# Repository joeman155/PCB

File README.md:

This is a repository of PCB (Printed Circuit Boards) that I have created.

internal_board - Internal board to the High Altitude Balloon that I am creating
                      - pcb1 - Arduino Shield with pressure sensor, serial voltage level converter, 
                               transistor for relay actuator circuit, circuitry for measuring psu voltage
                      - pcb3 - Copernicus GPS, Relay, PSU, switches, RFD900 power/data connectors.
                      - pcb4 - 5 volt 3amp Switch Mode PSU

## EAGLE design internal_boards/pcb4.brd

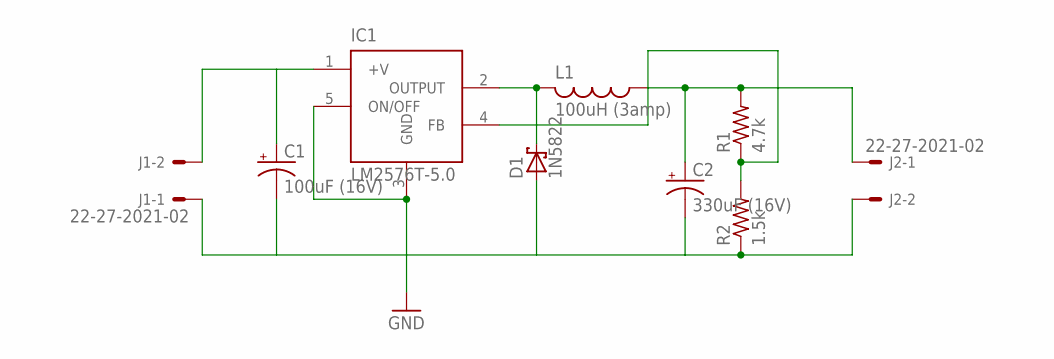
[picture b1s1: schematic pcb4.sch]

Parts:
C1: 100uF (16V); TT2D6
C2: 330uF (16V); TT5D10
D1: 1N5822; C4111-15
IC1: LM2576T-5.0; TO220-5
J1, J2: 22-27-2021-02; 6410-02
L1: 100uH (3amp); TJ3-U1
R1: 4.7k; 0204/7
R2: 1.5k; 0204/7

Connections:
GND: C1.-, C2.-, D1.A, IC1.3 (GND), IC1.5 (ON/OFF), J1.1, J2.2, R2.1
unnamed: IC1.4 (FB), R1.1, R2.2
unnamed: C1.+, IC1.1 (+V), J1.2
unnamed: D1.C, IC1.2 (OUTPUT), L1.2
unnamed: C2.+, J2.1, L1.1, R1.2

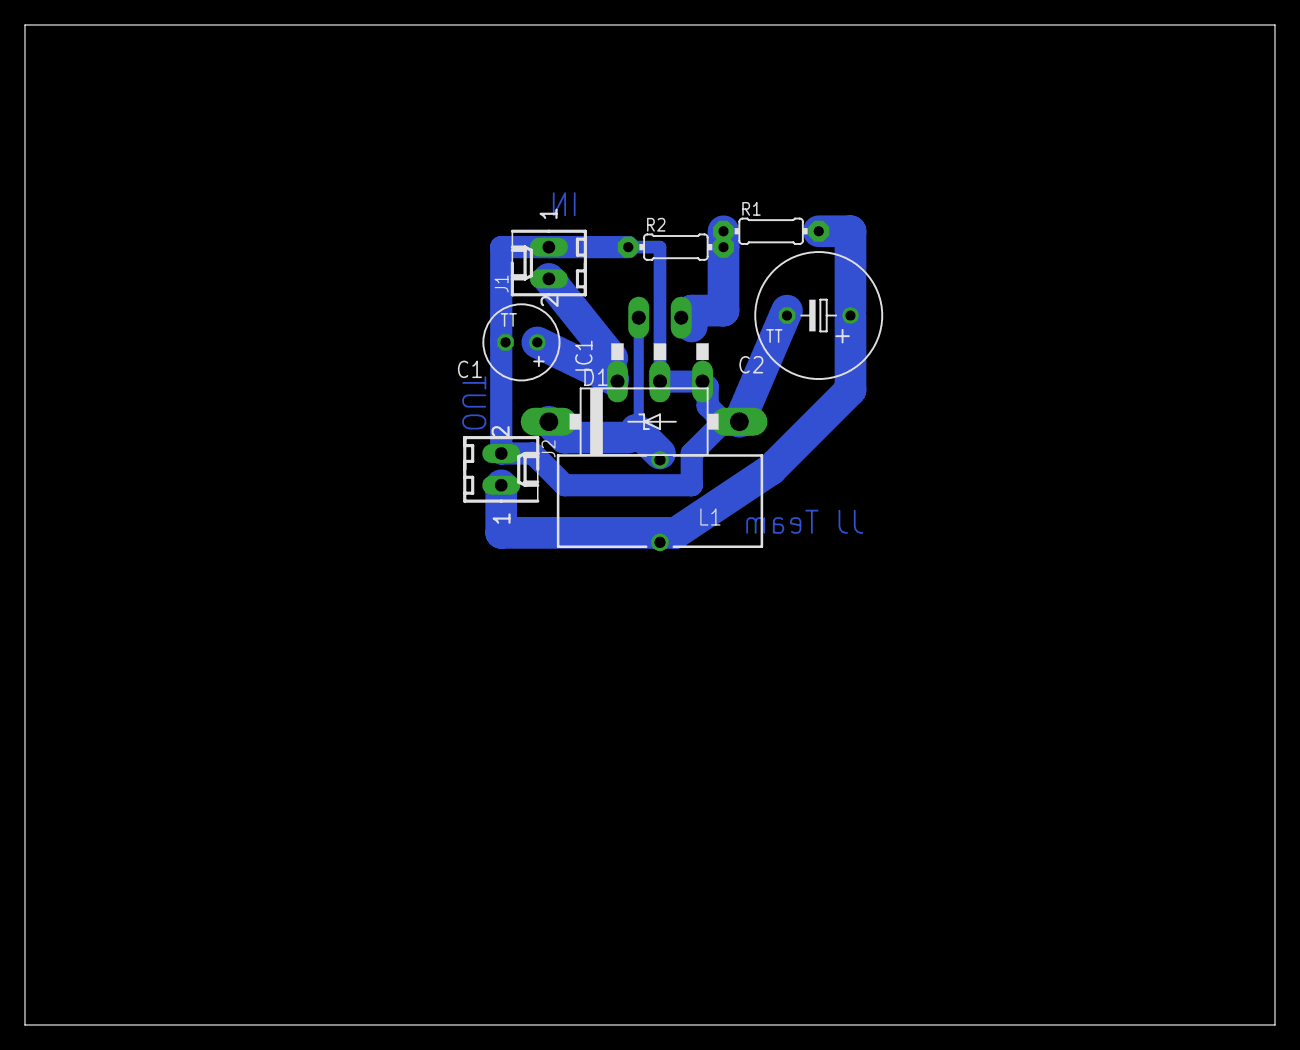
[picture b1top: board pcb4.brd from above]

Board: 2 copper layers, 100.0 x 80.0 mm, 9 parts (0 on the bottom side), 5 nets.

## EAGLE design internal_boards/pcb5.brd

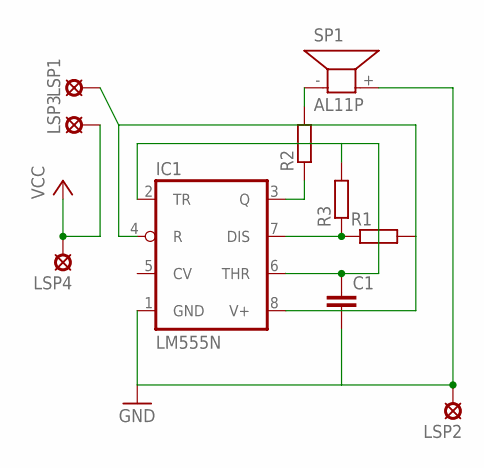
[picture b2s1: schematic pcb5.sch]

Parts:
C1: C-EU025-024X044; C025-024X044
IC1: LM555N; DIL08
LSP1, LSP2, LSP3, LSP4: MCS08
R1, R2: R-EU_0204_7; 0204/7
R3: R-EU_0204/7; 0204/7
SP1: AL11P

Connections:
GND: C1.2, IC1.1 (GND), LSP2.MP, SP1.+ (2)
unnamed: IC1.3 (Q), R2.1
unnamed: IC1.7 (DIS), R1.1, R3.1
unnamed: R2.2, SP1.- (1)
unnamed: C1.1, IC1.2 (TR), IC1.6 (THR), R3.2
unnamed: IC1.4 (R), IC1.8 (V+), LSP1.MP, R1.2
VCC: LSP3.MP, LSP4.MP

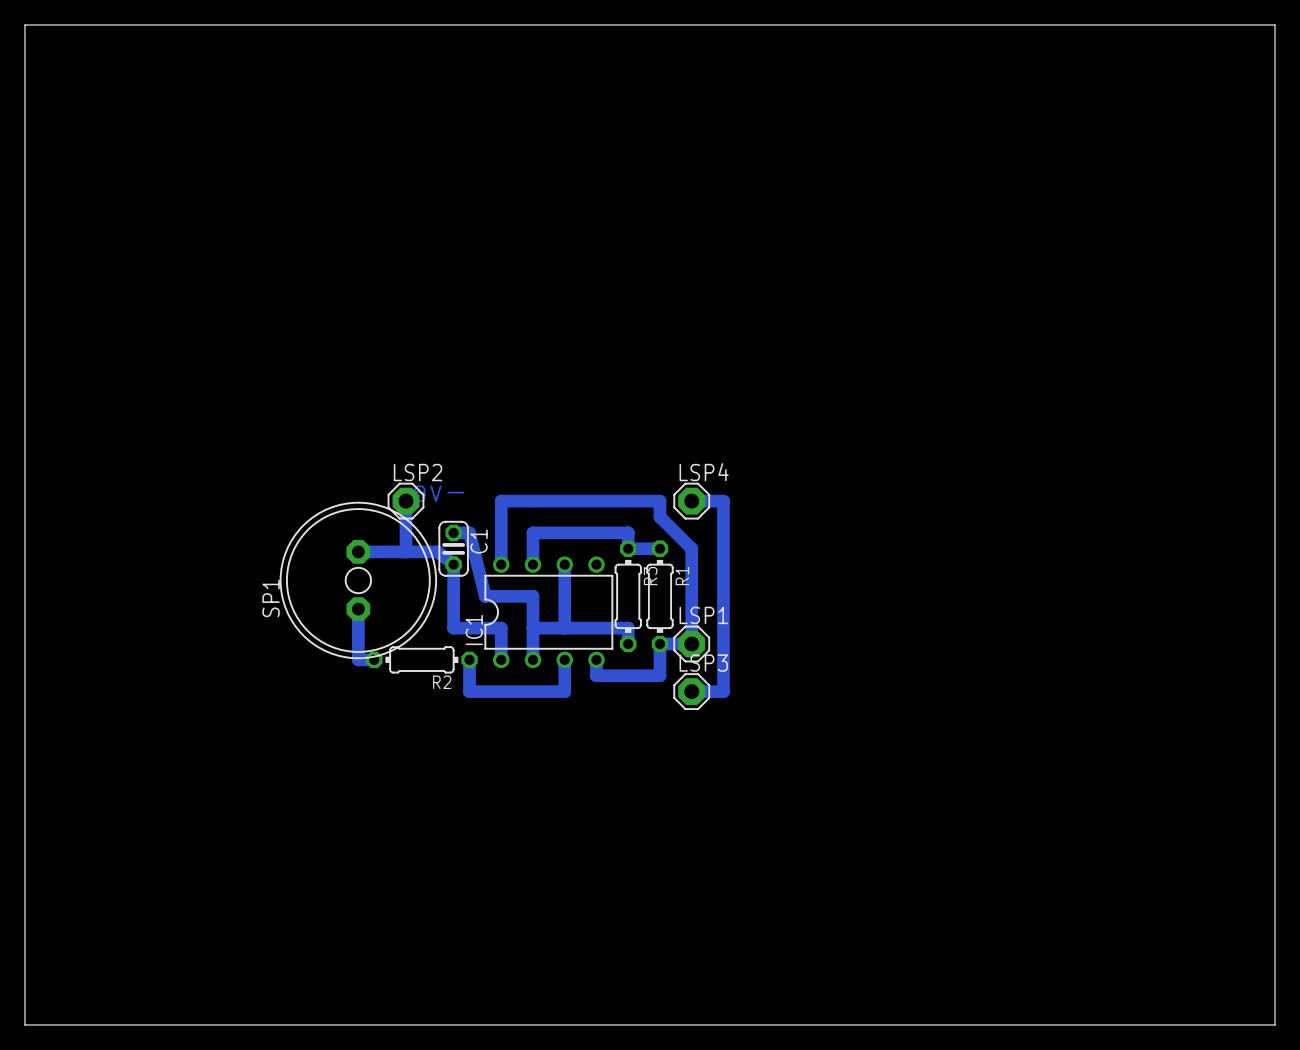
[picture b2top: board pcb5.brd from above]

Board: 2 copper layers, 100.0 x 80.0 mm, 10 parts (0 on the bottom side), 7 nets.

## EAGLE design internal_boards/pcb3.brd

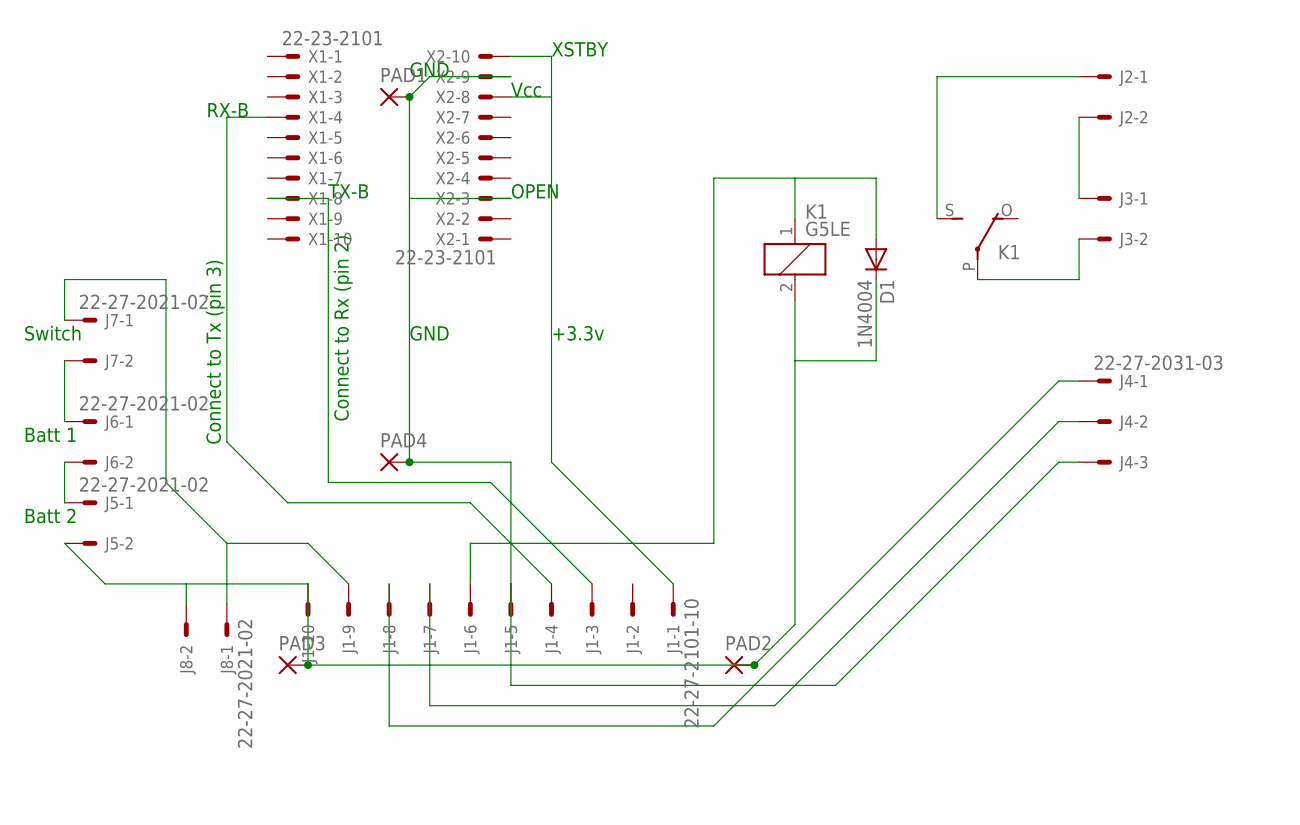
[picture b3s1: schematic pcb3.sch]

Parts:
D1: 1N4004; DO41-10
J1: 22-27-2101-10; 6410-10
J2, J3: KK-156-2
J4: 22-27-2031-03; 6410-03
J5, J6, J7, J8: 22-27-2021-02; 6410-02
K1: G5LE
PAD1, PAD2, PAD3, PAD4: 1,6/0,8
X1, X2: 22-23-2101

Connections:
unnamed: J1.1, X2.8, X2.10
unnamed: J1.9, J7.1, J8.1
unnamed: J1.4, X1.4
unnamed: J1.3, X1.8
unnamed: J1.5, J4.3, PAD1.1, PAD4.1, X2.3, X2.9
unnamed: D1.A, J1.6, K1.1
unnamed: J2.2, J3.1
unnamed: J3.2, K1.P
unnamed: J2.1, K1.S
unnamed: J1.7, J4.2
unnamed: J1.8, J4.1
unnamed: J5.1, J6.2
unnamed: J6.1, J7.2
unnamed: D1.C, J1.10, J5.2, J8.2, K1.2, PAD2.1, PAD3.1

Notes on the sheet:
RX-B
TX-B
XSTBY
GND
Vcc
OPEN
+3.3v
Connect to Rx (pin 2)
Connect to Tx (pin 3)
Switch
Batt 1
Batt 2

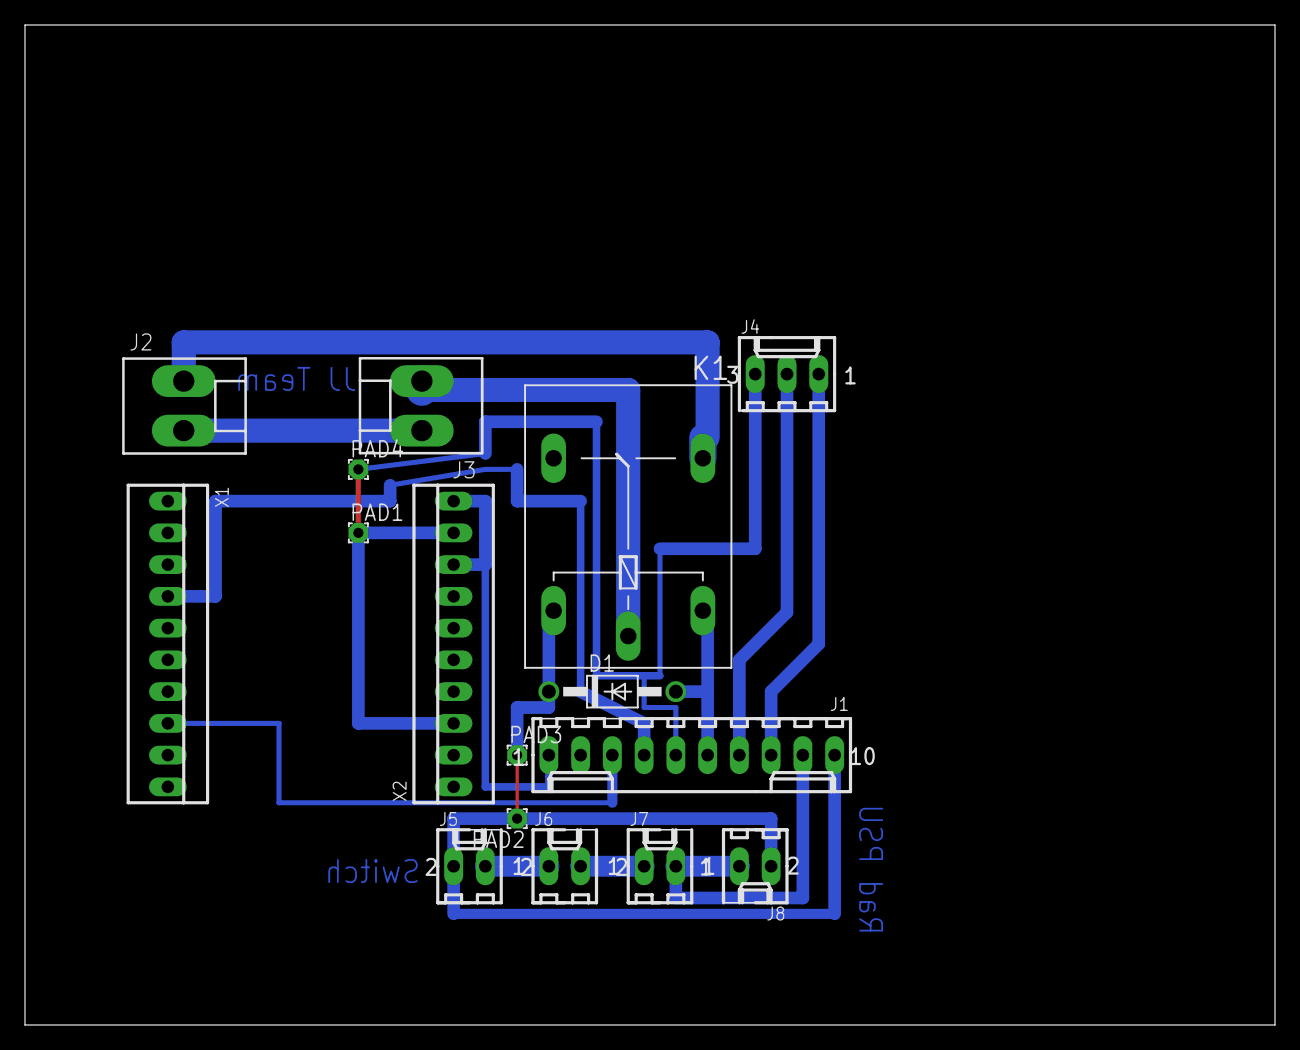
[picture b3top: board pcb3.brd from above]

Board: 2 copper layers, 100.0 x 80.0 mm, 16 parts (0 on the bottom side), 14 nets.

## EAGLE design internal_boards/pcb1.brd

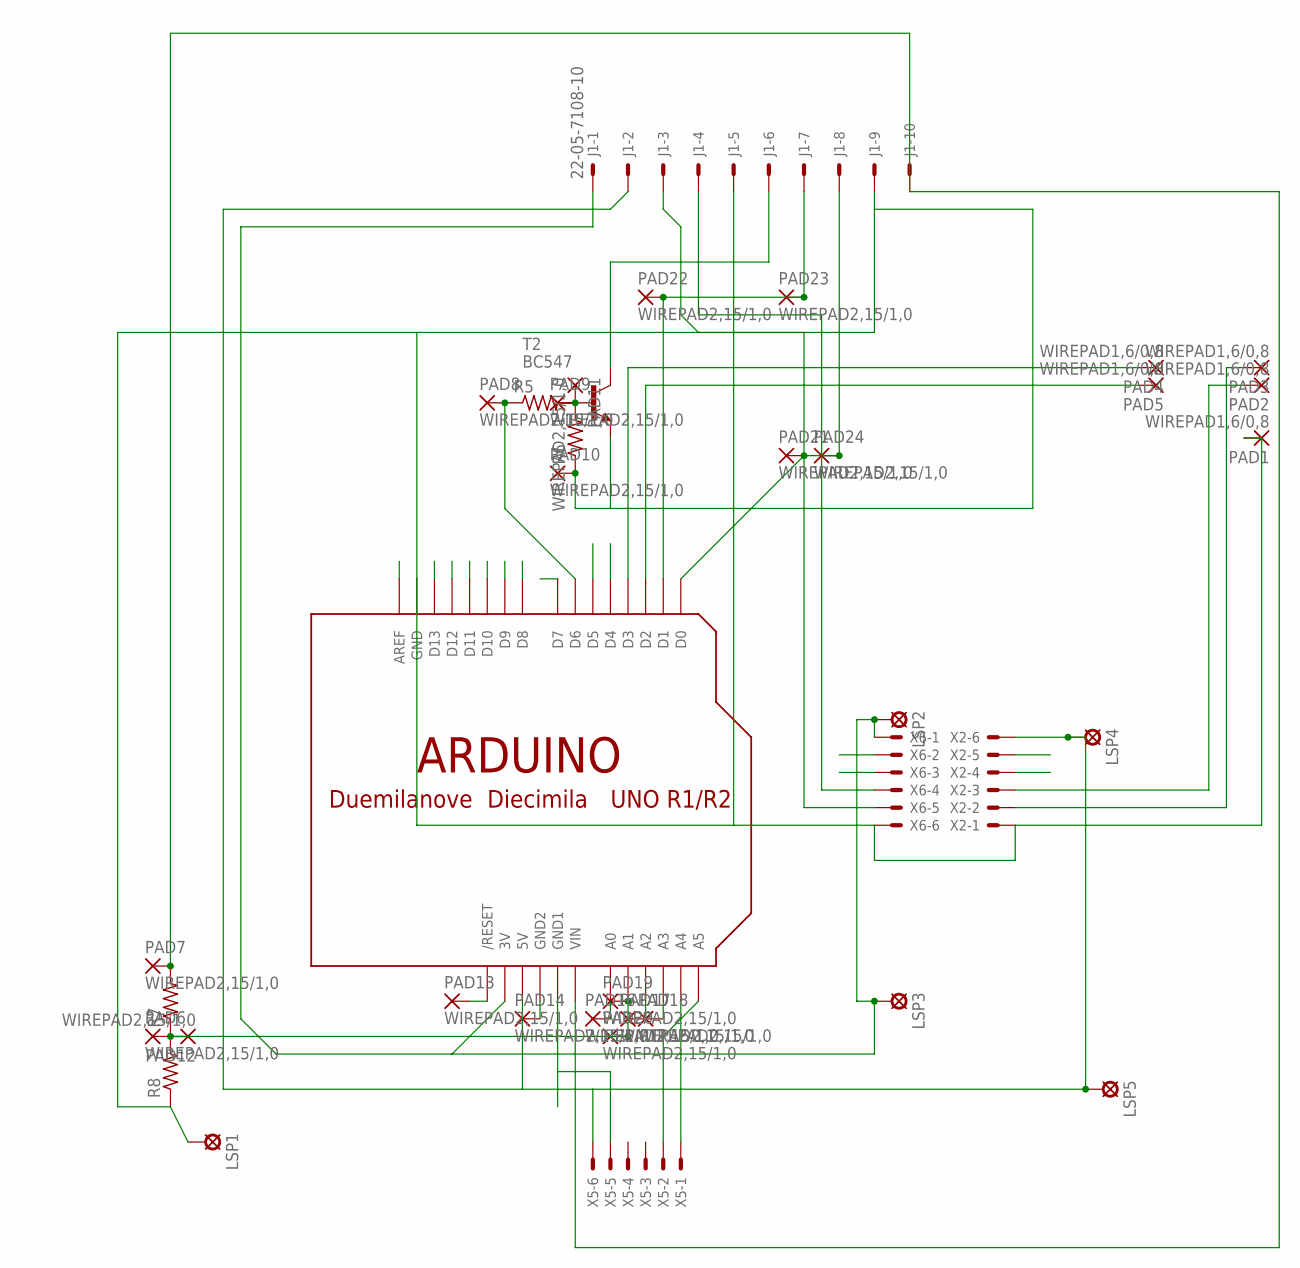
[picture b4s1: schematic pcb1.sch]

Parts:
J1: 22-05-7108-10; 7395-10
LSP1, LSP2, LSP3, LSP4, LSP5: LSP10
PAD1, PAD2, PAD3, PAD4, PAD5: WIREPAD1,6/0,8; 1,6/0,8
PAD6, PAD7, PAD8, PAD9, PAD10, PAD11, PAD12, PAD13, PAD14, PAD16, PAD17, PAD18, PAD19, PAD20, PAD21, PAD22, PAD23, PAD24: WIREPAD2,15/1,0; 2,15/1,0
R5, R6, R7, R8: R-US_0207/10; 0207/10
T2: BC547; TO92
U$1: ARDUINO-NODIM
X2, X5, X6: 22-23-2061

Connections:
unnamed: U$1.GND1, X5.5
unnamed: U$1.A5, X5.2
unnamed: U$1.A4, X5.1
unnamed: J1.6, T2.3 (C)
unnamed: PAD16.1, U$1.A0
unnamed: PAD17.1, U$1.A2
unnamed: PAD18.1, U$1.A3
unnamed: J1.5, J1.9, LSP1.MP, PAD1.1, PAD10.1, R6.1, R8.1, T2.1 (E), U$1.GND, X2.1, X6.6
unnamed: PAD6.1, PAD12.1, PAD19.1, PAD20.1, R7.1, R8.2, U$1.A1
unnamed: J1.2, LSP4.MP, LSP5.MP, U$1.5V, X2.6, X5.6
unnamed: PAD4.1, U$1.D3
unnamed: J1.1, LSP2.MP, LSP3.MP, U$1.3V, X6.1
unnamed: PAD5.1, U$1.D2
unnamed: J1.8, PAD21.1, PAD24.1, U$1.D0
unnamed: J1.7, PAD22.1, PAD23.1, U$1.D1
unnamed: PAD9.1, PAD11.1, R5.2, R6.2, T2.2 (B)
unnamed: PAD8.1, R5.1, U$1.D6
unnamed: J1.4, X6.4
unnamed: J1.3, X6.5
unnamed: PAD13.1, U$1.RESET (/RESET)
unnamed: PAD14.1, U$1.GND2
unnamed: J1.10, PAD7.1, R7.2, U$1.VIN
unnamed: PAD2.1, X2.3
unnamed: PAD3.1, X2.2

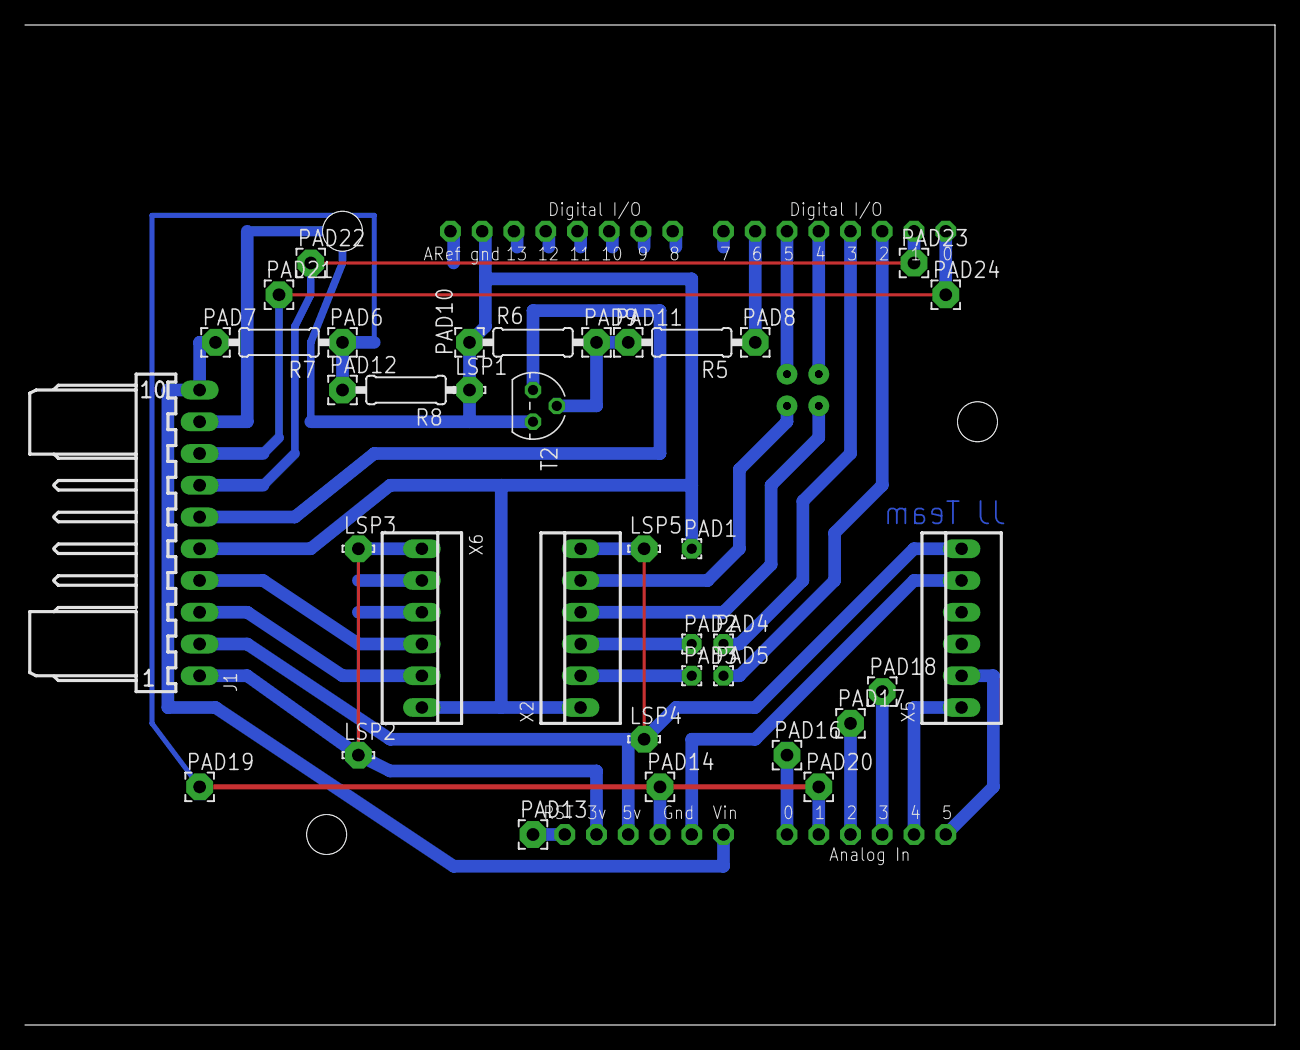
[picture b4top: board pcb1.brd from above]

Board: 2 copper layers, 100.0 x 80.0 mm, 38 parts (0 on the bottom side), 24 nets.

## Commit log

2014-03-27 Details on internal_board directory and contents
2014-04-22 * Adding pcb4 - which is a 5 volt, 3amp Switch Mode PSU
2014-04-22 * Added comments about new PCB
2014-09-13 * Adding new circuit diagram for squealer (to help direct recovery people to location of the balloon payload)
2014-09-13 * Adding in jumper for on/off
2015-07-11 * Enhancement to board to use regulator with pins slightly spaced out
2015-07-11 * Setting values of components in Schematic.
